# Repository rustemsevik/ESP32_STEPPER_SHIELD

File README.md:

# ESP32 Stepper Motor Shield

## 📌 Board Description
The **ESP32 Stepper Motor Shield** is a custom PCB designed for controlling up to **6 stepper motors** using an ESP32-DevKitC V4.

### Features
- **6 Stepper Motor Outputs** – Compatible with common StepStick driver modules (A4988, DRV8825).
- **12V Barrel Jack Input** – Powers all stepper drivers from a single source.
- **Minimal Design** – Compact layout for easy integration into projects.

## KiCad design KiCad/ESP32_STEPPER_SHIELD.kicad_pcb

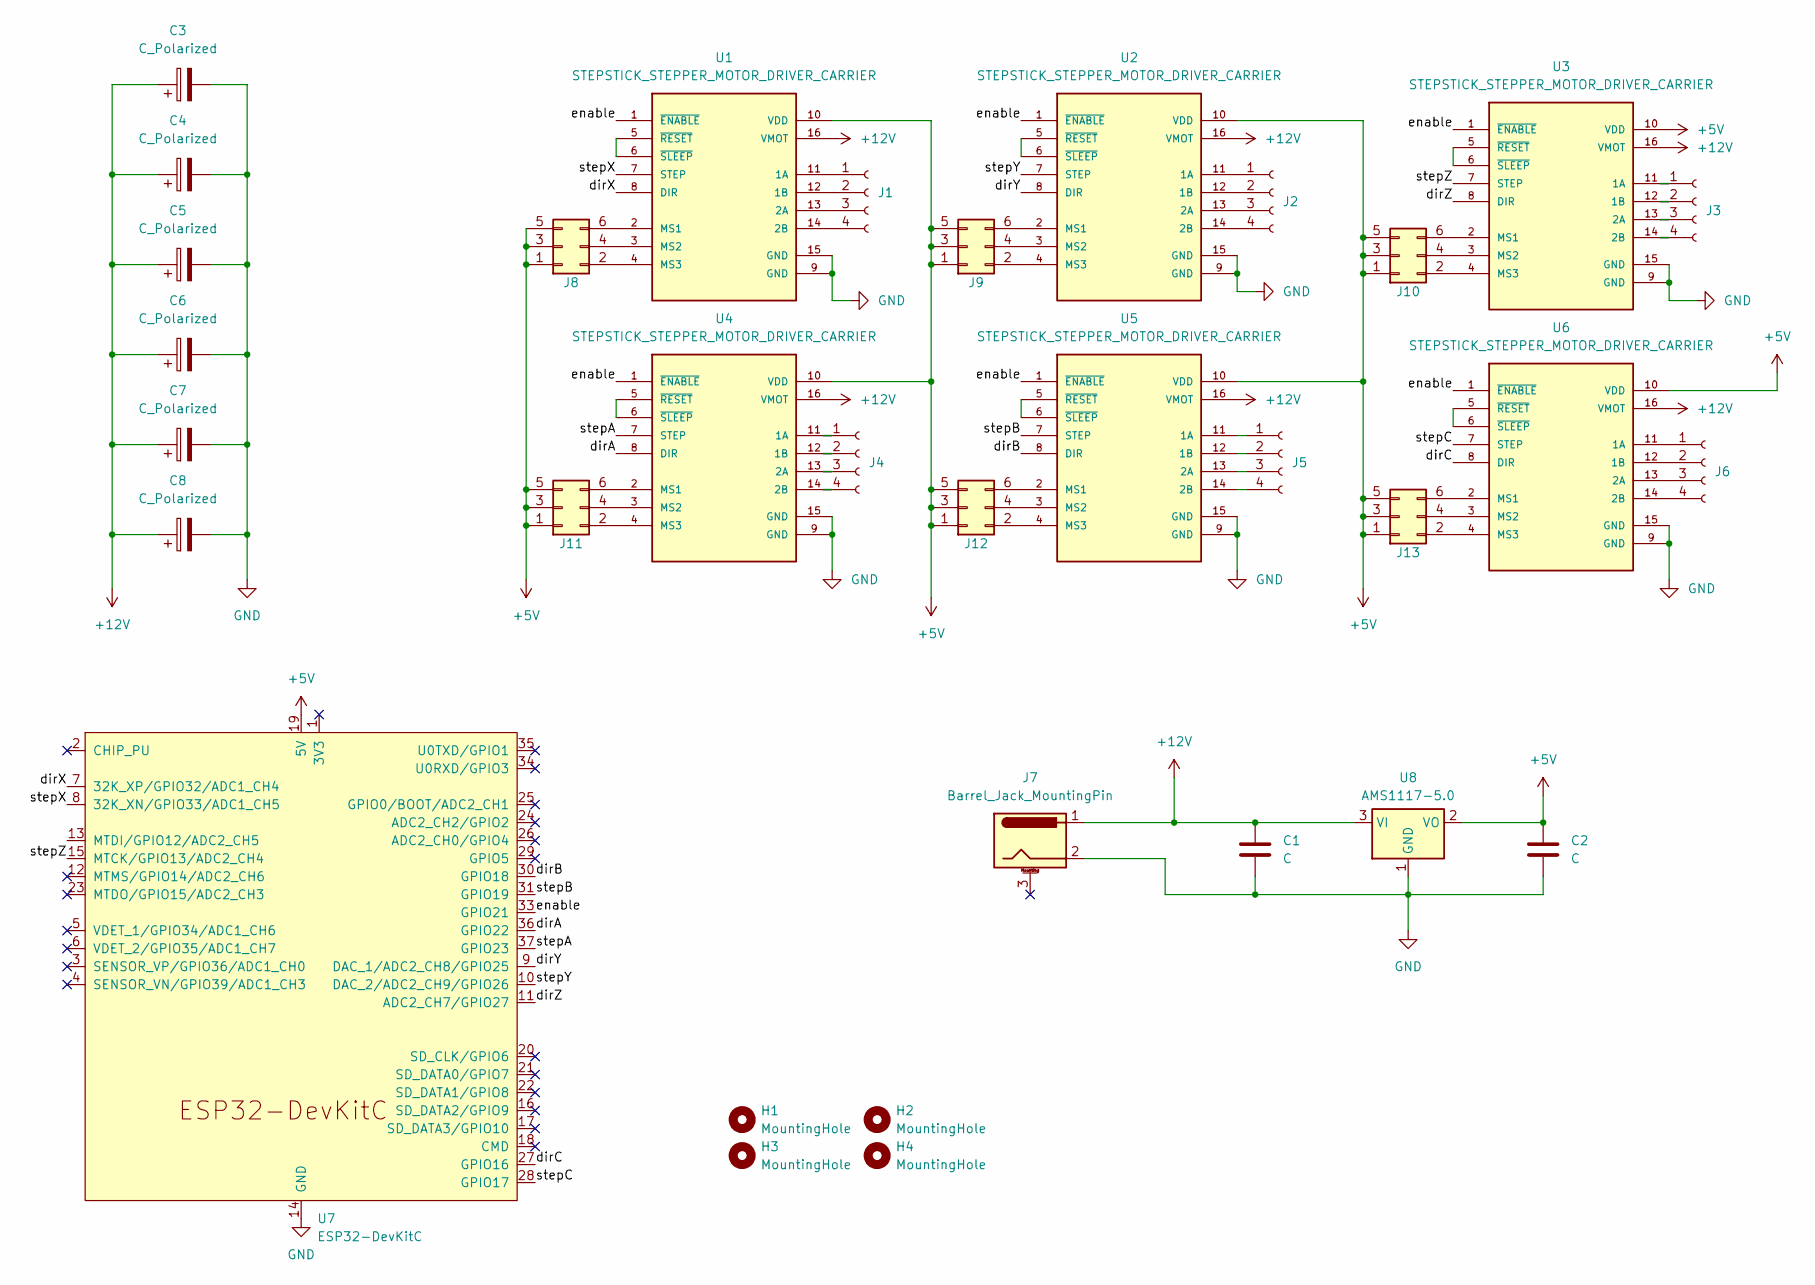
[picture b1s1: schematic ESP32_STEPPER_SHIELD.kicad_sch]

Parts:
C1: C; C_0603_1608Metric_Pad1.08x0.95mm_HandSolder
C2: C; C_1206_3216Metric_Pad1.33x1.80mm_HandSolder
C3, C4, C5, C6, C7, C8: C_Polarized; C_Elec_6.3x7.7
H1, H2, H3, H4: MountingHole; MountingHole_3mm
J1, J2, J3, J4, J5, J6: Conn_01x04_Socket; JST_XH_B4B-XH-A_1x04_P2.50mm_Vertical
J7: Barrel_Jack_MountingPin; BarrelJack_Horizontal
J8, J9, J10, J11, J12, J13: Conn_02x03_Odd_Even; PinHeader_2x03_P2.54mm_Vertical
U1, U2, U3, U4, U5, U6: STEPSTICK_STEPPER_MOTOR_DRIVER_CARRIER
U7: ESP32-DevKitC
U8: AMS1117-5.0; SOT-223-3_TabPin2

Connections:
+5V: C2.1, J8.1, J8.3, J8.5, J9.1, J9.3, J9.5, J10.1, J10.3, J10.5, J11.1, J11.3, J11.5, J12.1, J12.3, J12.5, J13.1, J13.3, J13.5, U1.10 (VDD), U2.10 (VDD), U3.10 (VDD), U4.10 (VDD), U5.10 (VDD), U6.10 (VDD), U7.19 (5V), U8.2 (VO)
+12V: C1.1, C3.1, C4.1, C5.1, C6.1, C7.1, C8.1, J7.1, U1.16 (VMOT), U2.16 (VMOT), U3.16 (VMOT), U4.16 (VMOT), U5.16 (VMOT), U6.16 (VMOT), U8.3 (VI)
/dirA: U4.8 (DIR), U7.36 (GPIO22)
/dirB: U5.8 (DIR), U7.30 (GPIO18)
/dirC: U6.8 (DIR), U7.27 (GPIO16)
/dirX: U1.8 (DIR), U7.7 (32K_XP/GPIO32/ADC1_CH4)
/dirY: U2.8 (DIR), U7.9 (DAC_1/ADC2_CH8/GPIO25)
/dirZ: U3.8 (DIR), U7.11 (ADC2_CH7/GPIO27)
/enable: U1.1 (~ENABLE), U2.1 (~ENABLE), U3.1 (~ENABLE), U4.1 (~ENABLE), U5.1 (~ENABLE), U6.1 (~ENABLE), U7.33 (GPIO21)
/stepA: U4.7 (STEP), U7.37 (GPIO23)
/stepB: U5.7 (STEP), U7.31 (GPIO19)
/stepC: U6.7 (STEP), U7.28 (GPIO17)
/stepX: U1.7 (STEP), U7.8 (32K_XN/GPIO33/ADC1_CH5)
/stepY: U2.7 (STEP), U7.10 (DAC_2/ADC2_CH9/GPIO26)
/stepZ: U3.7 (STEP), U7.15 (MTCK/GPIO13/ADC2_CH4)
GND: C1.2, C2.2, C3.2, C4.2, C5.2, C6.2, C7.2, C8.2, J7.2, U1.9 (GND), U1.15 (GND), U2.9 (GND), U2.15 (GND), U3.9 (GND), U3.15 (GND), U4.9 (GND), U4.15 (GND), U5.9 (GND), U5.15 (GND), U6.9 (GND), U6.15 (GND), U7.14 (GND), U7.32 (GND), U7.38 (GND), U8.1 (GND)
unnamed: J1.1, U1.11 (1A)
unnamed: J1.2, U1.12 (1B)
unnamed: J1.3, U1.13 (2A)
unnamed: J1.4, U1.14 (2B)
unnamed: J2.1, U2.11 (1A)
unnamed: J2.2, U2.12 (1B)
unnamed: J2.3, U2.13 (2A)
unnamed: J2.4, U2.14 (2B)
unnamed: J3.1, U3.11 (1A)
unnamed: J3.2, U3.12 (1B)
unnamed: J3.3, U3.13 (2A)
unnamed: J3.4, U3.14 (2B)
unnamed: J4.1, U4.11 (1A)
unnamed: J4.2, U4.12 (1B)
unnamed: J4.3, U4.13 (2A)
unnamed: J4.4, U4.14 (2B)
unnamed: J5.1, U5.11 (1A)
unnamed: J5.2, U5.12 (1B)
unnamed: J5.3, U5.13 (2A)
unnamed: J5.4, U5.14 (2B)
unnamed: J6.1, U6.11 (1A)
unnamed: J6.2, U6.12 (1B)
unnamed: J6.3, U6.13 (2A)
unnamed: J6.4, U6.14 (2B)
unnamed: J8.2, U1.4 (MS3)
unnamed: J8.4, U1.3 (MS2)
unnamed: J8.6, U1.2 (MS1)
unnamed: J9.2, U2.4 (MS3)
unnamed: J9.4, U2.3 (MS2)
unnamed: J9.6, U2.2 (MS1)
unnamed: J10.2, U3.4 (MS3)
unnamed: J10.4, U3.3 (MS2)
unnamed: J10.6, U3.2 (MS1)
unnamed: J11.2, U4.4 (MS3)
unnamed: J11.4, U4.3 (MS2)
unnamed: J11.6, U4.2 (MS1)
unnamed: J12.2, U5.4 (MS3)
unnamed: J12.4, U5.3 (MS2)
unnamed: J12.6, U5.2 (MS1)
unnamed: J13.2, U6.4 (MS3)
unnamed: J13.4, U6.3 (MS2)
unnamed: J13.6, U6.2 (MS1)
unnamed: U1.5 (~RESET), U1.6 (~SLEEP)
unnamed: U2.5 (~RESET), U2.6 (~SLEEP)
unnamed: U3.5 (~RESET), U3.6 (~SLEEP)
unnamed: U4.5 (~RESET), U4.6 (~SLEEP)
unnamed: U5.5 (~RESET), U5.6 (~SLEEP)
unnamed: U6.5 (~RESET), U6.6 (~SLEEP)

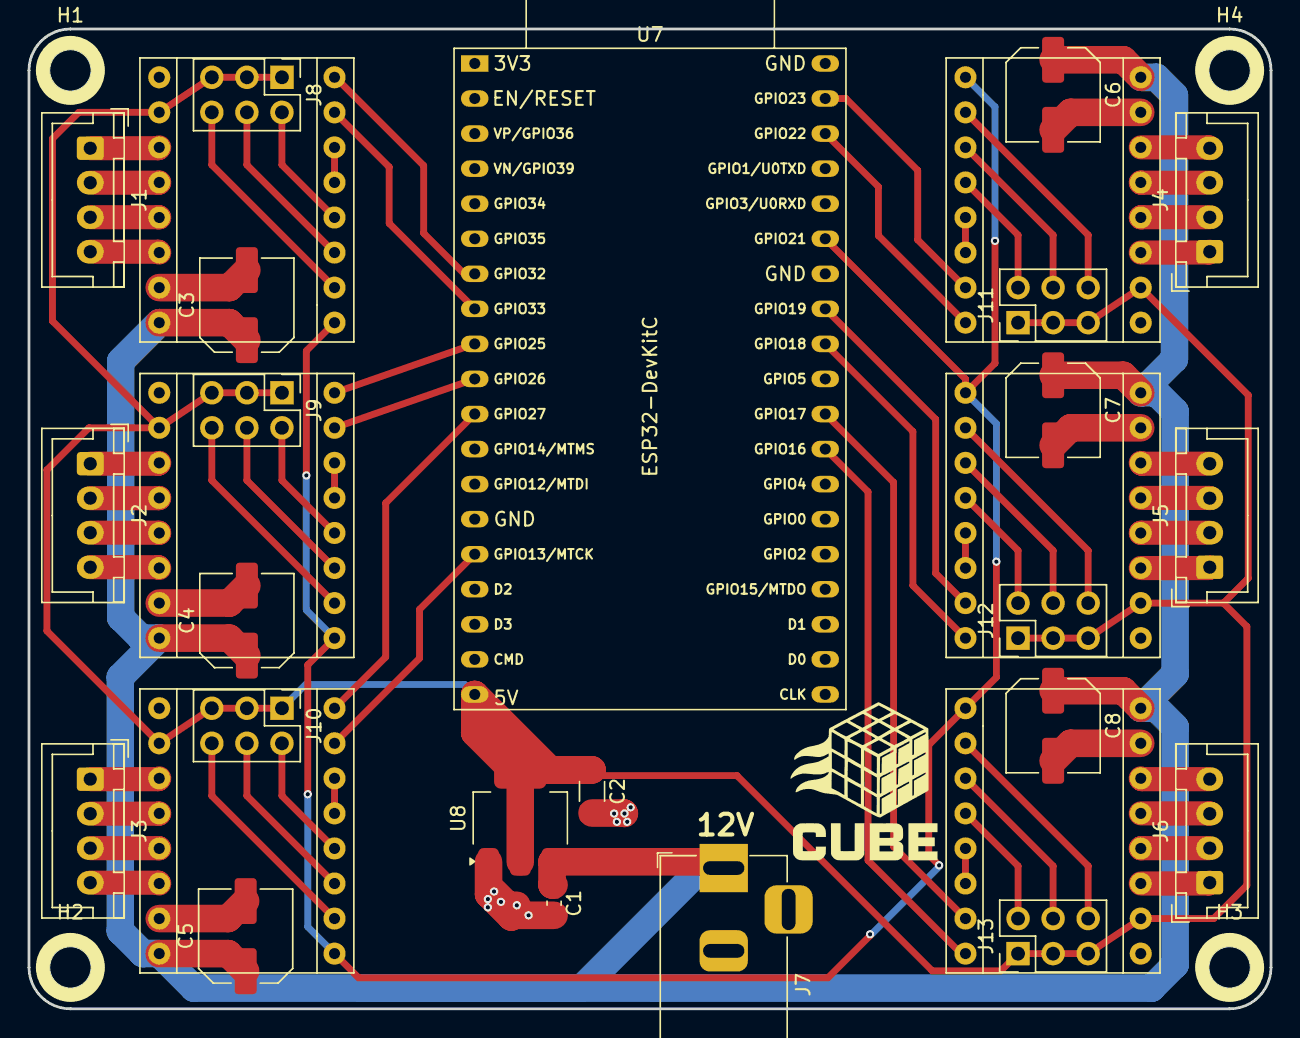
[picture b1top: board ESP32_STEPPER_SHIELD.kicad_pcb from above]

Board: 2 copper layers, 90.0 x 71.0 mm, 33 parts (0 on the bottom side), 64 nets.
